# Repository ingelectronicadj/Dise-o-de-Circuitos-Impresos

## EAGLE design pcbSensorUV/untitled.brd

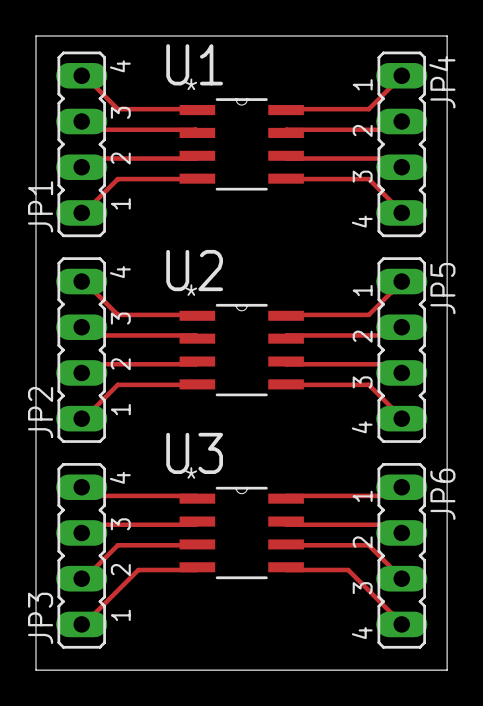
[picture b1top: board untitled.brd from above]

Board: 2 copper layers, 22.8 x 35.2 mm, 9 parts (0 on the bottom side), 24 nets.

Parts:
JP1, JP2, JP3, JP4, JP5, JP6: JP4
U1, U2, U3: OPA842ID; SOIC127P600X175-8N

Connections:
unnamed: JP1.4, U1.1
unnamed: JP1.3, U1.2
unnamed: JP1.2, U1.3
unnamed: JP1.1, U1.4
unnamed: JP4.4, U1.5
unnamed: JP4.3, U1.6
unnamed: JP4.2, U1.7
unnamed: JP4.1, U1.8
unnamed: JP2.4, U2.1
unnamed: JP2.3, U2.2
unnamed: JP2.2, U2.3
unnamed: JP2.1, U2.4
unnamed: JP5.4, U2.5
unnamed: JP5.3, U2.6
unnamed: JP5.2, U2.7
unnamed: JP5.1, U2.8
unnamed: JP3.4, U3.1
unnamed: JP3.3, U3.2
unnamed: JP3.2, U3.3
unnamed: JP3.1, U3.4
unnamed: JP6.4, U3.5
unnamed: JP6.2, U3.7
unnamed: JP6.1, U3.8
unnamed: JP6.3, U3.6
